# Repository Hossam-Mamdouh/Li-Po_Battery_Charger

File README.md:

PowerCore 3V3

USB-C 1S Li-Po Power Management & 3.3 V Supply PCB

PowerCore 3V3 is a compact power-management board for a single-cell
Li-Po battery. It combines USB-C input, Li-Po charging, system
power-path management, battery protection, and a regulated 3.3 V output.

Features

USB-C 5 V power input

1S Li-Po battery support

MCP73871 charger with system power-path management

DW01A + FS8205A battery protection

TPS63802 buck-boost regulator

Regulated 3.3 V output

Designed for up to 500 mA system load

Approximately 500 mA maximum programmed charge current

USB input PTC protection

Charge/status indication LEDs

Power Architecture

USB-C 5 V
    |
    v
Input Protection
    |
    v
MCP73871 Charger + Power Path
    |                    |
    v                    v
1S Li-Po               VSYS
    |                    |
    v                    v
DW01A + FS8205A      TPS63802
Battery Protection   Buck-Boost
                         |
                         v
                       3.3 V
                         |
                         v
                    System Load

Main Components

Reference   Component      Function

U2          MCP73871       Li-Po charger and power-path controller
U3          DW01A          Battery protection controller
Q1          FS8205A        Dual N-channel MOSFET protection switch
U4          TPS63802       Buck-boost regulator
F1          1.5 A PTC      USB input over-current protection
J1          USB-C          5 V power input
Battery     JST-PH 2-pin   1S Li-Po connection

Charger Configuration

Charge Current

PROG1 = 2 kΩ

Programs approximately 500 mA maximum charge current.

The actual charging current is reduced when system load consumes part of
the available input power.

Termination Current

PROG3 = 20 kΩ

Sets approximately 50 mA termination current.

Input Current Mode

SEL = +5V_USB

The charger uses the higher-current adapter mode rather than the 500 mA
USB mode.

Other Settings

CE pulled high → charging enabled

TE# tied to GND → safety timer enabled

THERM uses a fixed 10 kΩ resistor to GND

VPCC tied to +5V_USB

PROG2 pulled high through 10 kΩ

PG# pulled high through 10 kΩ

STAT1 / STAT2 provide status indication

Battery Protection

The protection stage uses a DW01A controller and FS8205A dual MOSFET.

For the selected FUXINSEMI FS8205A:

Pin 1 → S1
Pin 2 → D1/D2
Pin 3 → S2
Pin 4 → G2
Pin 5 → D1/D2
Pin 6 → G1

Pins 2 and 5 are the common drain connection and must be electrically
connected.

External connections:

Q1 S1      → B-
Q1 S2      → GND / P-
Q1 G1      → DW01A OD
Q1 G2      → DW01A OC
Q1 D1/D2   → common drain node

DW01A current sense:

CSI → 1 kΩ → GND / P-

3.3 V Regulation

The TPS63802 maintains a regulated 3.3 V rail from the 1S battery/system
rail.

Intended load: 500 mA

Inductor: 0.47 µH

Input capacitor: 10 µF

Output capacitor: 22 µF

Feedback: 511 kΩ / 91 kΩ

EN: VSYS

MODE: GND

The buck-boost topology allows 3.3 V regulation as battery voltage moves
above and below the output voltage.

USB-C Interface

The USB-C connector is configured as a power input.

CC1 → 5.1 kΩ → GND
CC2 → 5.1 kΩ → GND

Input decoupling and transient protection are included.

Battery Connector

The current schematic uses:

Battery Pin 2 → VBAT (+)
Battery Pin 1 → B- (-)

JST-PH pin numbering does not inherently define battery polarity. Verify
the actual battery cable/mating connector pinout before connection.

Clearly mark + and − on the PCB.

Power Budget

The intended system load is:

3.3 V × 500 mA = 1.65 W

The programmed 500 mA battery charge current is a maximum. Actual charge
current depends on system load, USB supply capability, regulator
efficiency, and charger operating conditions.

PCB Layout Guidelines

Keep TPS63802 input/output capacitors close to the IC.

Keep the 0.47 µH inductor close to the switching pins.

Keep the FB trace away from switching nodes.

Use short, low-impedance high-current paths.

Place USB input protection close to the USB-C connector.

Use appropriate copper width for battery and system power paths.

Provide solid ground copper and thermal areas.

Clearly mark battery polarity.

Design Status

Revision: A
Status: Prototype / Engineering Design

Before manufacturing, verify:

Schematic ERC

PCB DRC

Q1 symbol-to-footprint pin mapping

Battery connector pinout

PTC fuse rating and thermal derating

USB-C input capability

TPS63802 thermal performance

Charger behavior under simultaneous load and charging

Battery protection thresholds

Applications

Embedded systems

IoT devices

Portable electronics

Battery-powered sensors

ESP32-based products

Automation systems

Custom electronics prototypes

Tools

KiCad 10.x

LCSC components where applicable

Author

Hossam Mamdouh
Embedded Systems Engineer

Portfolio: https://hossam-mamdouh.github.io/

License

Choose an appropriate hardware/software license before public release.

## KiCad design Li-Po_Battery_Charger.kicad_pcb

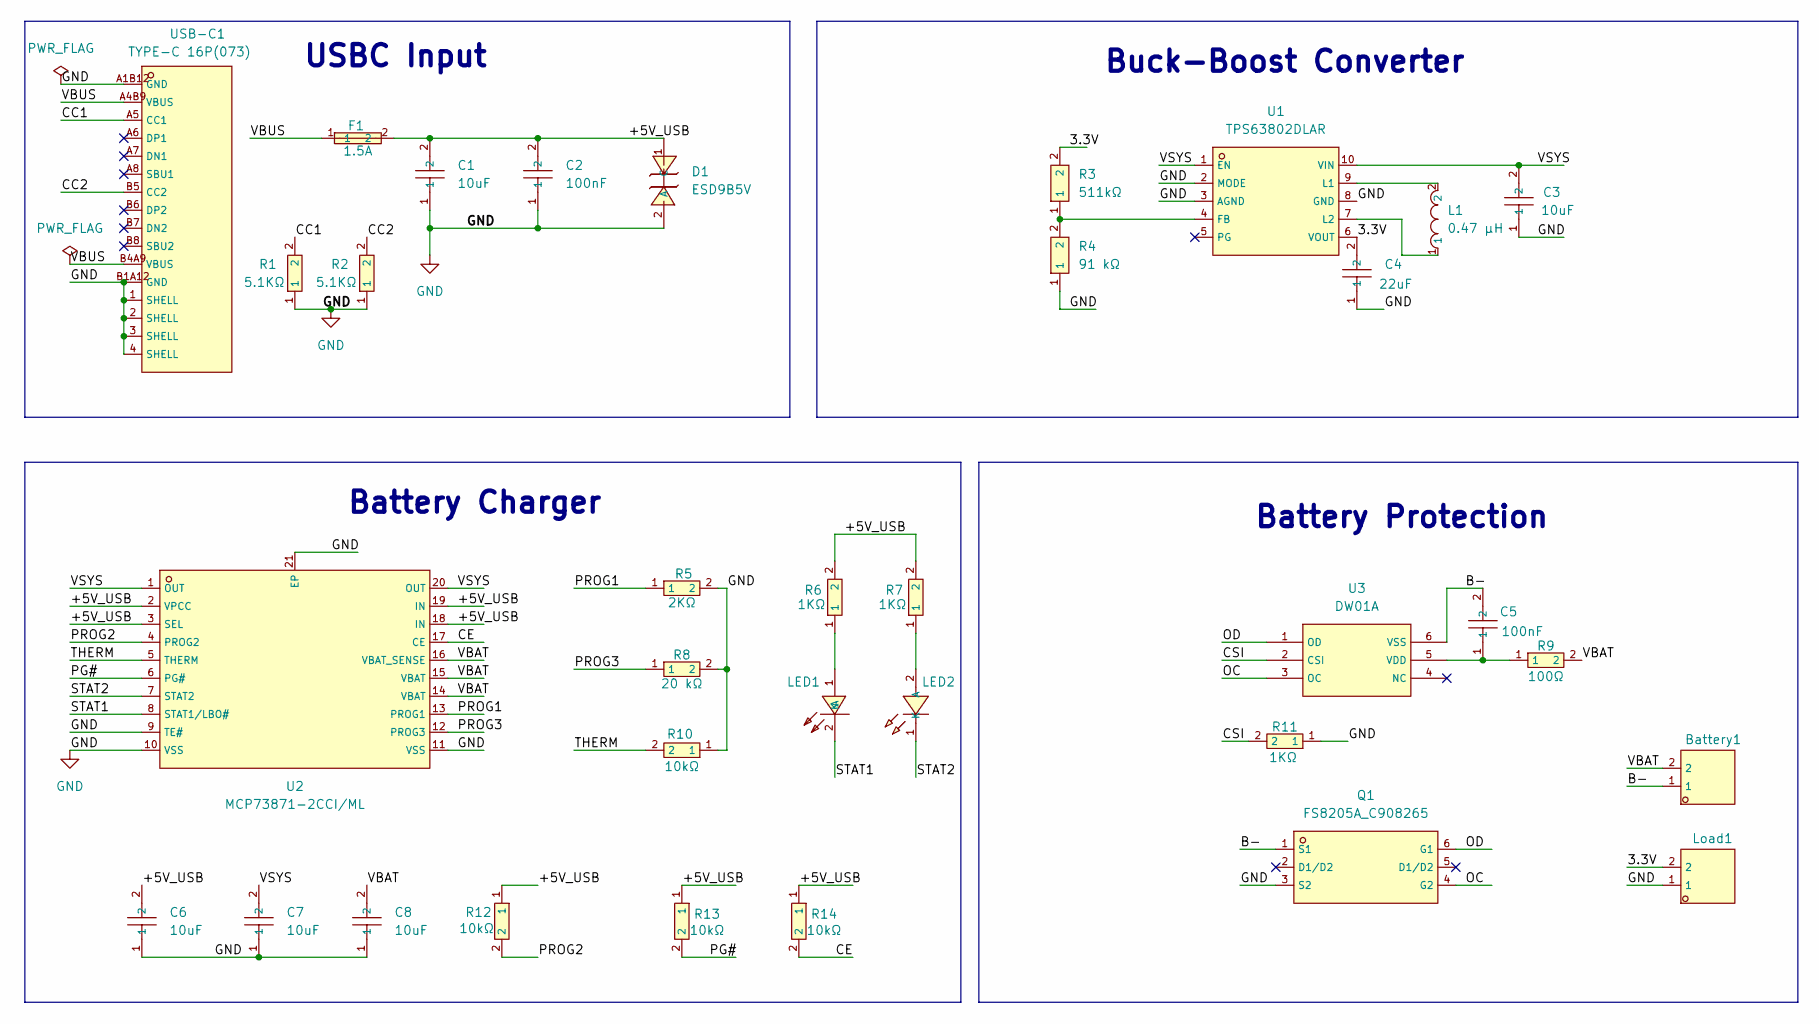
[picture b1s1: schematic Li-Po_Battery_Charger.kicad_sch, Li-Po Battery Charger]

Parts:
Battery1: S2B-PH-K-S(LF)(SN); C173752_CONN-TH_S2B-PH-K-S-LF-SN; LCSC C173752
C1, C3, C6, C7, C8: 10uF; C3039641_C0603; LCSC C3039641
C2: 100nF; C5448791_C0402; LCSC C5448791
C4: 22uF; C22367828_C0603; LCSC C22367828
C5: 100nF; C5137616_C0603; LCSC C5137616
D1: ESD9B5V; C2905646_SOD-923_L0_8-W0_6-LS1_0-BI-1; LCSC C2905646
F1: 1.5A; C118413_F1206; LCSC C118413
L1: 0.47 µH; C285747_IND-SMD_L4_0-W4_0_CHILISIN_MHCI04012N; LCSC C285747
LED1: 0603; C2286_LED-SMD_L1_6-W0_8-R-RD; LCSC C2286
LED2: PSC-1608U52GC-G4; C22371297_LED0603-RD_GREEN; LCSC C22371297
Load1: S2B-PH-K-S(LF)(SN); C173752_CONN-TH_S2B-PH-K-S-LF-SN; LCSC C173752
Q1: FS8205A_C908265; C908265_SOT-23-6_L2_9-W1_6-P0_95-LS2_8-BR; LCSC C908265
R1, R2: 5.1KΩ; C25905_R0402; LCSC C25905
R3: 511kΩ; C861454_R0603; LCSC C861454
R4: 91 kΩ; C2907077_R0603; LCSC C2907077
R5: 2KΩ; C4109_R0402; LCSC C4109
R6, R7, R11: 1KΩ; C11702_R0402; LCSC C11702
R8: 20 kΩ; C93942_R0402; LCSC C93942
R9: 100Ω; C106232_R0402; LCSC C106232
R10, R12, R13, R14: 10kΩ; C326912_R0402; LCSC C326912
U1: TPS63802DLAR; C2845237_VSON-10_L3_0-W2_0-P0_50-TL; LCSC C2845237
U2: MCP73871-2CCI/ML; C5121473_QFN-20_L4_0-W4_0-P0_50-BL-EP2_7; LCSC C5121473
U3: DW01A; C42459937_SOT-23-6_L2_9-W1_6-P0_95-LS2_8-BL; LCSC C42459937
USB-C1: TYPE-C 16P(073); C668624_USB-C-SMD_TYPE-C16PIN_C668624; LCSC C668624

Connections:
/3.3V: C4.2, Load1.2, R3.2, U1.6 (VOUT); also elsewhere on the board
/+5V_USB: C1.2, C2.2, C6.2, D1.1 (C), F1.2, R6.2, R7.2, R12.1, R13.1, R14.1, U2.2 (VPCC), U2.3 (SEL), U2.18 (IN), U2.19 (IN)
/B-: Battery1.1, C5.2, Q1.1 (S1), U3.6 (VSS); also elsewhere on the board
/CC1: R1.2, USB-C1.A5 (CC1); also elsewhere on the board
/CC2: R2.2, USB-C1.B5 (CC2); also elsewhere on the board
/CE: R14.2, U2.17 (CE)
/CSI: R11.2, U3.2 (CSI)
/OC: Q1.4 (G2), U3.3 (OC)
/OD: Q1.6 (G1), U3.1 (OD)
/PG#: R13.2, U2.6 (PG#)
/PROG1: R5.1, U2.13 (PROG1)
/PROG2: R12.2, U2.4 (PROG2)
/PROG3: R8.1, U2.12 (PROG3)
/STAT1: LED1.2 (K), U2.8 (STAT1/LBO#)
/STAT2: LED2.1 (K), U2.7 (STAT2)
/THERM: R10.2, U2.5 (THERM)
/VBAT: Battery1.2, C8.2, R9.2, U2.14 (VBAT), U2.15 (VBAT), U2.16 (VBAT_SENSE); also elsewhere on the board
/VBUS: F1.1, USB-C1.A4B9 (VBUS), USB-C1.B4A9 (VBUS); also elsewhere on the board
/VSYS: C3.2, C7.2, U1.1 (EN), U1.10 (VIN), U2.1 (OUT), U2.20 (OUT)
GND: C1.1, C2.1, C3.1, C4.1, C6.1, C7.1, C8.1, D1.2 (A), Load1.1, Q1.3 (S2), R1.1, R2.1, R4.1, R5.2, R8.2, R10.1, R11.1, U1.2 (MODE), U1.3 (AGND), U1.8 (GND), U2.9 (TE#), U2.10 (VSS), U2.11 (VSS), U2.21 (EP), USB-C1.1 (SHELL), USB-C1.2 (SHELL), USB-C1.3 (SHELL), USB-C1.4 (SHELL), USB-C1.A1B12 (GND), USB-C1.B1A12 (GND); also elsewhere on the board
unnamed: LED1.1 (A), R6.1
unnamed: LED2.2 (A), R7.1
unnamed: R3.1, R4.2, U1.4 (FB)
unnamed: L1.2, U1.9 (L1)
unnamed: L1.1, U1.7 (L2)
unnamed: C5.1, R9.1, U3.5 (VDD)

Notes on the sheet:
USBC Input
Battery Charger
Battery Protection
Buck-Boost Converter

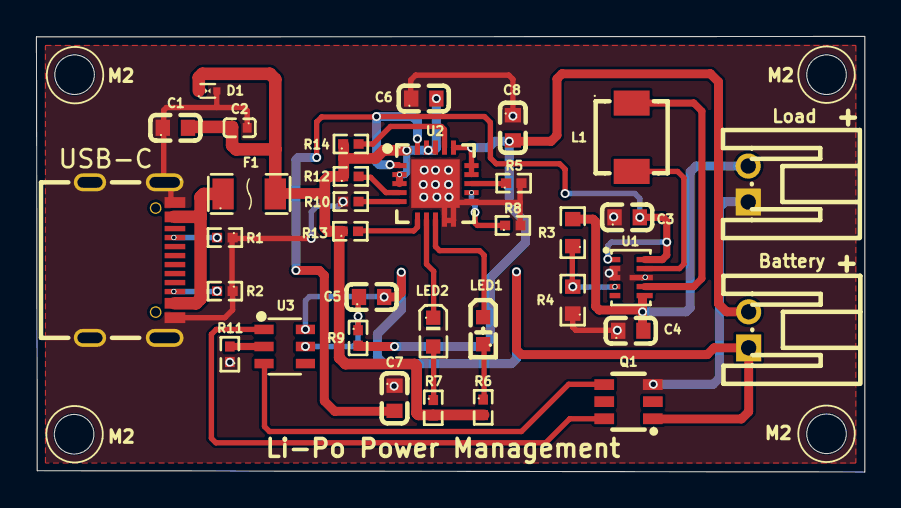
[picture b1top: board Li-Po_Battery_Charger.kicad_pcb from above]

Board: 2 copper layers, 46.0 x 24.2 mm, 34 parts (0 on the bottom side), 26 nets.

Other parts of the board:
Battery: S2B-PH-K-S(LF)(SN); C173752_CONN-TH_S2B-PH-K-S-LF-SN
Load: S2B-PH-K-S(LF)(SN); C173752_CONN-TH_S2B-PH-K-S-LF-SN
USB-C: TYPE-C 16P(073); C668624_USB-C-SMD_TYPE-C16PIN_C668624

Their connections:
/3.3V: Load.2; also elsewhere on the board
/B-: Battery.1; also elsewhere on the board
/CC1: USB-C.A5 (CC1); also elsewhere on the board
/CC2: USB-C.B5 (CC2); also elsewhere on the board
/VBAT: Battery.2; also elsewhere on the board
/VBUS: USB-C.A4B9 (VBUS), USB-C.B4A9 (VBUS); also elsewhere on the board
GND: Load.1, USB-C.1 (SHELL), USB-C.2 (SHELL), USB-C.3 (SHELL), USB-C.4 (SHELL), USB-C.A1B12 (GND), USB-C.B1A12 (GND); also elsewhere on the board
